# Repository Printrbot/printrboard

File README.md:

printrboard
===========

Reprap Electronics for the Printrbot

For more info see the Reprap wiki page http://reprap.org/wiki/Printrboard

The BoM with Digikey P/N's is available here: https://goo.gl/G4QnvK

This project, and all of its design files (including the layout), is licensed under the [Creative Commons Attribution-ShareAlike 3.0 Unported](http://creativecommons.org/licenses/by-sa/3.0/) license.

Anyone found to be in violation of this license may not produce or discribute any products using these designs, and will have legal action taken against them.

If you do end up producing boards commercially, a donation of 5% of the retail price or $4 per board would greatly be appreciated. Paypal (lwalkera at ieee.org), or bitcoin 1Cy1JwPiEEVS1RYxfHHFcmJMKbFNrb1Nqd work the best.

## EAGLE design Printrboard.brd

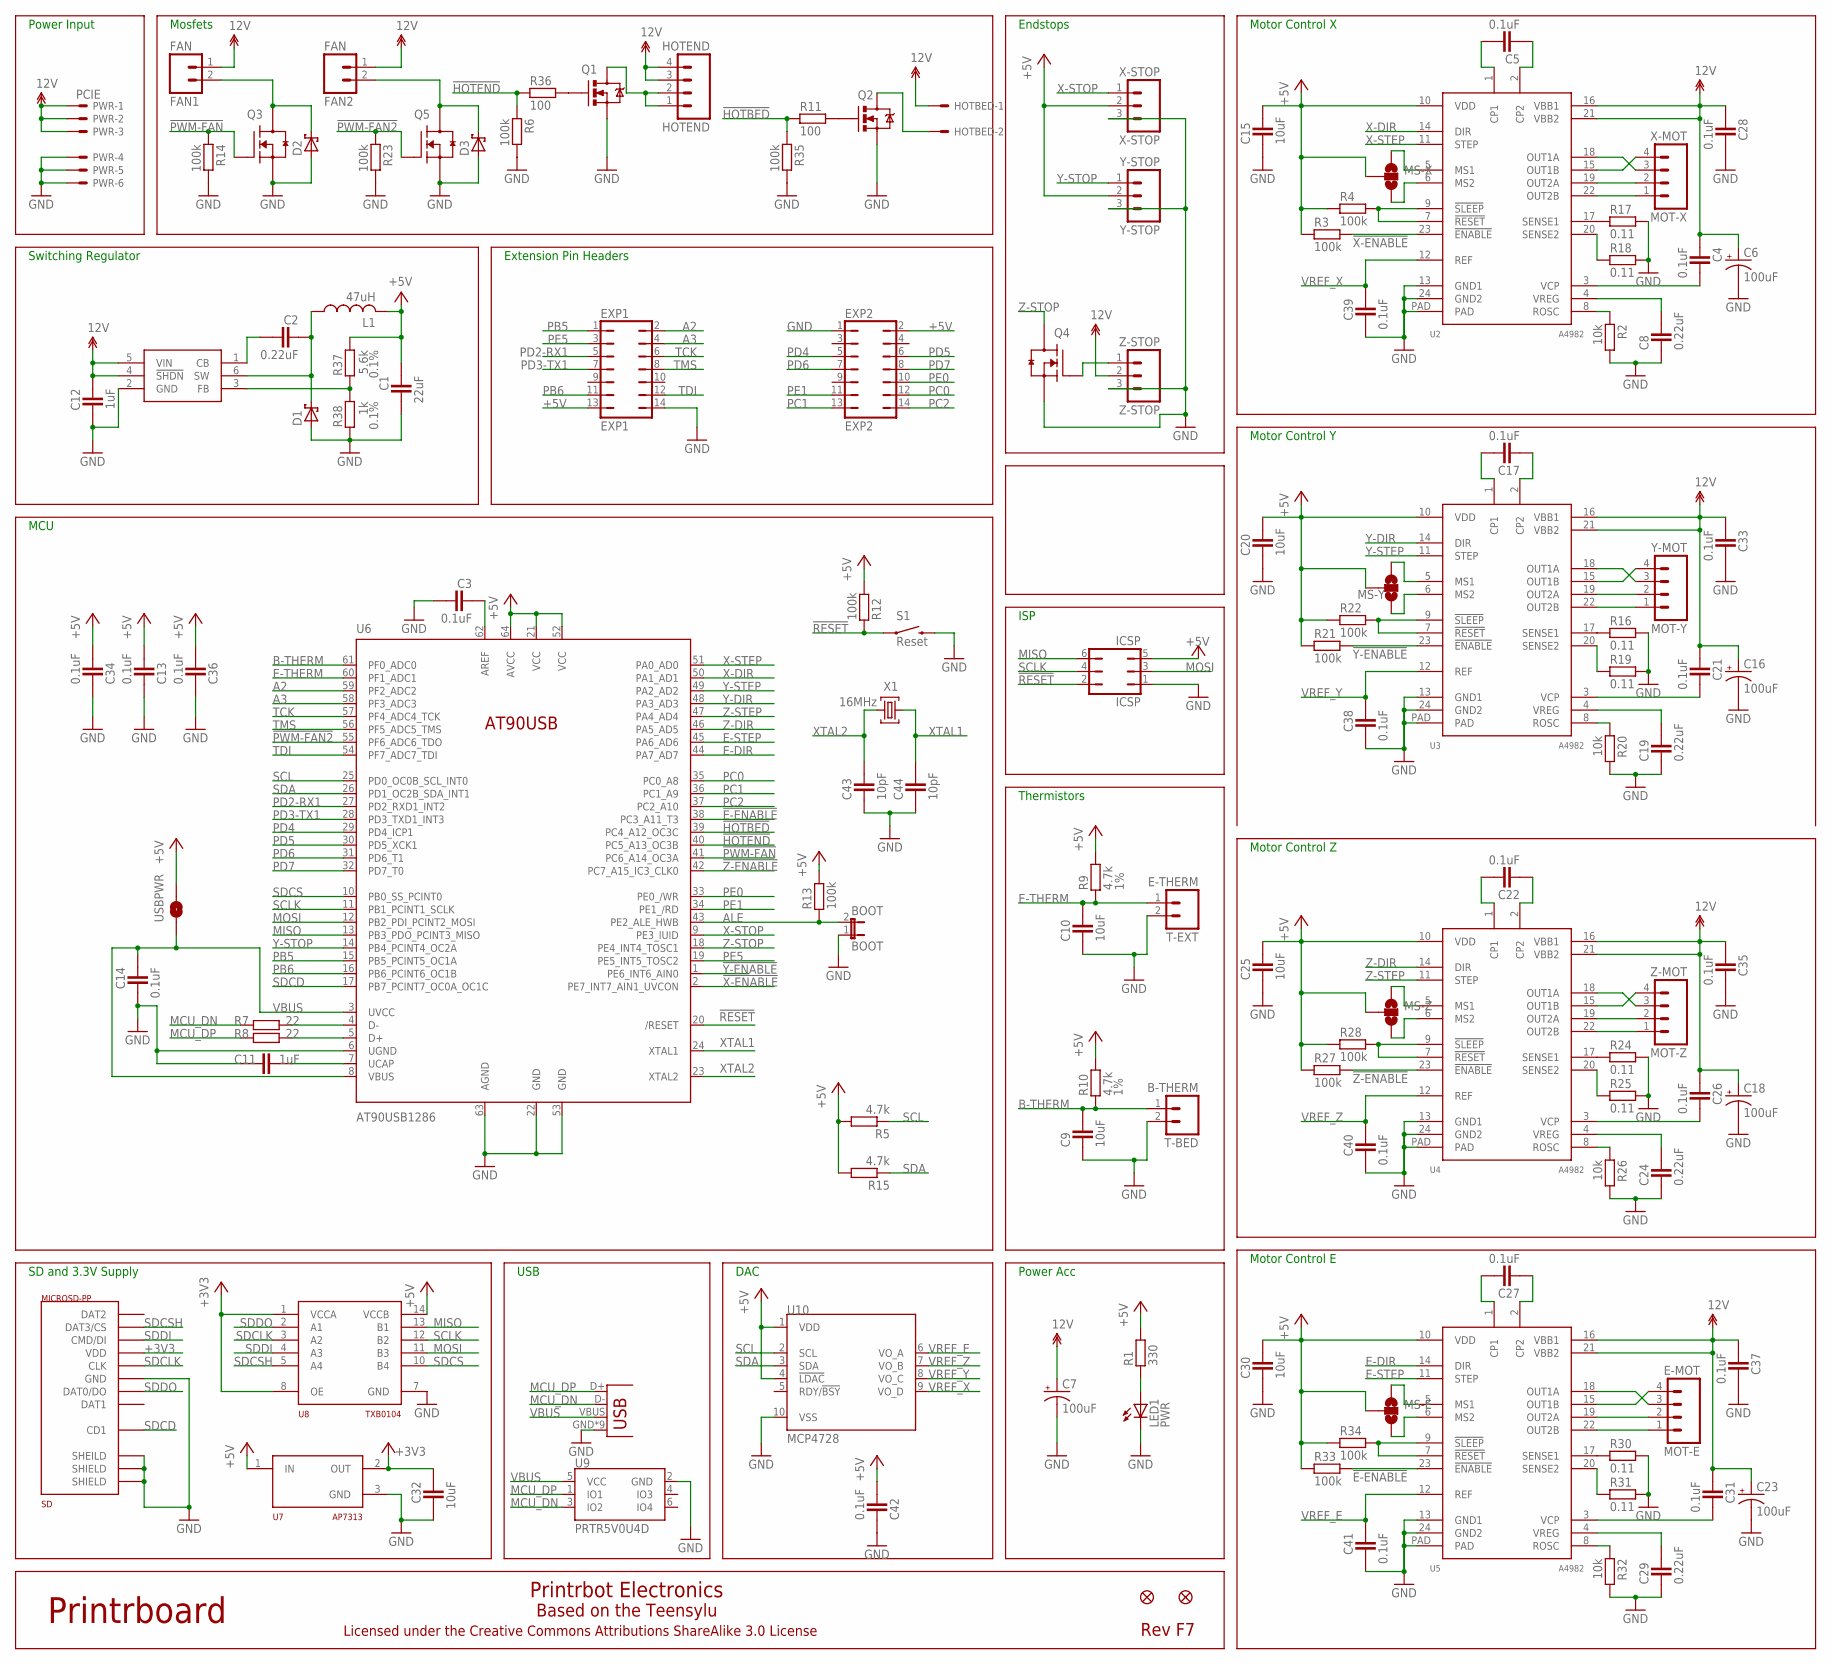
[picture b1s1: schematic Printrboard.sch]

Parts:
BOOT: BOOT; 1X02
C1: 22uF; CAPC2012X145AN
C2, C8, C19, C24, C29: 0.22uF; CAPC2012X145AN
C3, C4, C5, C13, C14, C17, C21, C22, C26, C27, C28, C31, C33, C34, C35, C36, C37, C38, C39, C40, C41, C42: 0.1uF; CAPC2012X145AN
C6, C7, C16, C18, C23: 100uF; PANASONIC_D
C9, C10, C15, C20, C25, C30, C32: 10uF; CAPC2012X145AN
C11, C12: 1uF; CAPC2012X145AN
C43, C44: 10pF; CAPC2012X145AN
D1, D2, D3: SCH-DIODESMA; SMA
E-MOT: MOT-E; MOLEX-1X4
EXP1: EXP1; JP7Q
EXP2: EXP2; JP7Q
FAN1, FAN2: FAN; 1X02
HOTBED: PHOENIX-2POS-5MM-SCREW; PHOENIX-5MM-2POS
HOTEND: HOTEND; MOLEX-1X4
ICSP: ICSP; JP3Q
JP26, JP33: FIDUCIAL1X2.5; FIDUCIAL-1X2.5
L1: 47uH; SDR1006
LED1: PWR; CHIP-LED0805
MS-E: SOLDERJUMPER_2WAYCONNECTED; SJ_3_CONNECTED
MS-X: SOLDERJUMPER_2WAYCONNECTED; SJ_3_CONNECTED
MS-Y: SOLDERJUMPER_2WAYCONNECTED; SJ_3_CONNECTED
MS-Z: SOLDERJUMPER_2WAYCONNECTED; SJ_3_CONNECTED
PWR: PCIE; 5566-6
Q1, Q2: RFP30N06LE; TO220V
Q3, Q4, Q5: RFP30N06LE; SOT95P280X135-3N
R1: 330; RESC2012X70N
R2, R20, R26, R32: 10k; RESC2012X70N
R3, R4, R6, R12, R13, R14, R21, R22, R23, R27, R28, R33, R34, R35: 100k; RESC2012X70N
R5, R15: 4.7k; RESC2012X70N
R7, R8: 22; RESC2012X70N
R9, R10: 4.7k; RESC2012X70N; TOLERANCE 1%
R11, R36: 100; RESC2012X70N
R16, R17, R18, R19, R24, R25, R30, R31: 0.11; RESC2012X70N
R37: 5.6k; RESC2012X70N; TOLERANCE 0.1%
R38: 1k; RESC2012X70N; TOLERANCE 0.1%
S1: Reset; TACTILE_SWITCH_TALL
SD: MICROSD-PP; USD-101-00660-68-6
T-BED: B-THERM; 1X02
T-EXT: E-THERM; 1X02
U1: LM2841; TSOT6
U2, U3, U4, U5: A4982; TSSOP-24
U6: AT90USB1286; TQFP64-2
U7: AP7313; SOT23C
U8: TXB0104; TSSOP14
U9: PRTR5V0U4D; SOT23-6
U10: MCP4728; MSOP10
USB-M: USB-MICRO-PTH; USB-MICROB-PTH
USBPWR: SOLDERJUMPERNO; SJ_2S-NO
X1: 16MHz; NDK-XTAL
X-MOT: MOT-X; MOLEX-1X4
X-STOP: X-STOP; MOLEX-1X3
Y-MOT: MOT-Y; MOLEX-1X4
Y-STOP: Y-STOP; MOLEX-1X3
Z-MOT: MOT-Z; MOLEX-1X4
Z-STOP: Z-STOP; MOLEX-1X3

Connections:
12V: C4.1, C6.+, C7.+, C12.1, C16.+, C18.+, C21.1, C23.+, C26.1, C28.1, C31.1, C33.1, C35.1, C37.1, FAN1.1, FAN2.1, HOTBED.P$1, HOTEND.3, HOTEND.4, PWR.1, PWR.2, PWR.3, U1.4 (!SHDN), U1.5 (VIN), U2.16 (VBB1), U2.21 (VBB2), U3.16 (VBB1), U3.21 (VBB2), U4.16 (VBB1), U4.21 (VBB2), U5.16 (VBB1), U5.21 (VBB2), Z-STOP.2
!E-ENABLE: R33.2, U5.23 (!ENABLE), U6.38 (PC3_A11_T3)
!HOTBED: R11.1, R35.1, U6.39 (PC4_A12_OC3C)
!HOTEND: R6.1, R36.1, U6.40 (PC5_A13_OC3B)
!PWM-FAN: Q3.1 (G), R14.1, U6.41 (PC6_A14_OC3A)
!PWM-FAN2: Q5.1 (G), R23.1, U6.55 (PF6_ADC6_TDO)
!RESET: ICSP.2, R12.1, S1.A2 (1), U6.20 (/RESET)
!X-ENABLE: R3.2, U2.23 (!ENABLE), U6.2 (PE7_INT7_AIN1_UVCON)
!Y-ENABLE: R21.2, U3.23 (!ENABLE), U6.1 (PE6_INT6_AIN0)
!Z-ENABLE: R27.2, U4.23 (!ENABLE), U6.42 (PC7_A15_IC3_CLK0)
+3V3: C32.1, SD.P$4 (VDD), U7.2 (OUT), U8.1 (VCCA), U8.8 (OE)
+5V: C1.1, C13.2, C15.2, C20.2, C25.2, C30.2, C34.2, C36.2, C42.2, EXP1.13, EXP2.2, ICSP.5, L1.P$2 (2), MS-E.2, MS-X.2, MS-Y.2, MS-Z.2, R1.2, R3.1, R4.1, R5.2, R9.2, R10.2, R12.2, R13.2, R15.2, R21.1, R22.1, R27.1, R28.1, R33.1, R34.1, R37.1, U2.10 (VDD), U3.10 (VDD), U4.10 (VDD), U5.10 (VDD), U6.21 (VCC), U6.52 (VCC), U6.64 (AVCC), U7.1 (IN), U8.14 (VCCB), U10.1 (VDD), U10.4 (!LDAC), USBPWR.2, X-STOP.2, Y-STOP.2
A2: EXP1.2, U6.59 (PF2_ADC2)
A3: EXP1.4, U6.58 (PF3_ADC3)
ALE: BOOT.2, R13.1, U6.43 (PE2_ALE_HWB)
AREF: C3.1, U6.62 (AREF)
B-THERM: C9.2, R10.1, T-BED.1, U6.61 (PF0_ADC0)
E-DIR: U5.14 (DIR), U6.44 (PA7_AD7)
E-STEP: U5.11 (STEP), U6.45 (PA6_AD6)
E-THERM: C10.2, R9.1, T-EXT.1, U6.60 (PF1_ADC1)
GND: BOOT.1, C1.2, C3.2, C6.-, C7.-, C8.1, C9.1, C10.1, C11.1, C12.2, C13.1, C14.2, C15.1, C16.-, C18.-, C19.1, C20.1, C23.-, C24.1, C25.1, C28.2, C29.1, C30.1, C32.2, C33.2, C34.1, C35.2, C36.1, C37.2, C38.2, C39.2, C40.2, C41.2, C42.1, C43.1, C44.1, D1.A, D2.A, D3.A, EXP1.14, EXP2.1, ICSP.1, LED1.C, PWR.4, PWR.5, PWR.6, Q1.3 (S), Q2.3 (S), Q3.2 (S), Q4.2 (S), Q5.2 (S), R2.2, R6.2, R14.2, R16.2, R17.2, R18.2, R19.2, R20.2, R23.2, R24.2, R25.2, R26.2, R30.2, R31.2, R32.2, R35.2, R38.2, S1.B2 (2), SD.GND1 (SHEILD), SD.GND2 (SHIELD), SD.GND3 (SHIELD), SD.P$6 (GND), T-BED.2, T-EXT.2, U1.2 (GND), U2.13 (GND1), U2.24 (GND2), U2.PAD, U3.13 (GND1), U3.24 (GND2), U3.PAD, U4.13 (GND1), U4.24 (GND2), U4.PAD, U5.13 (GND1), U5.24 (GND2), U5.PAD, U6.6 (UGND), U6.22 (GND), U6.53 (GND), U6.63 (AGND), U7.3 (GND), U8.7 (GND), U9.2 (GND), U10.10 (VSS), USB-M.GND, USB-M.GND1 (GND), USB-M.GND2 (GND), USB-M.GND3 (GND), USB-M.GND4 (GND), USB-M.GND5 (GND), USB-M.GND6 (GND), USB-M.GND7 (GND), USB-M.GND8 (GND), X-STOP.3, Y-STOP.3, Z-STOP.3
HOTBED-GND: HOTBED.P$2, Q2.2 (D)
HOTEND-GND: HOTEND.1, HOTEND.2, Q1.2 (D)
MCU_DN: R7.1, U9.3 (IO2), USB-M.D-
MCU_DP: R8.1, U9.1 (IO1), USB-M.D+
MISO: ICSP.6, U6.13 (PB3_PDO_PCINT3_MISO), U8.13 (B1)
MOSI: ICSP.3, U6.12 (PB2_PDI_PCINT2_MOSI), U8.11 (B3)
unnamed: LED1.A, R1.1
unnamed: D2.C, FAN1.2, Q3.3 (D)
unnamed: R7.2, U6.4 (D-)
unnamed: R8.2, U6.5 (D+)
unnamed: Q4.1 (G), Z-STOP.1
unnamed: Q2.1 (G), R11.2
unnamed: D3.C, FAN2.2, Q5.3 (D)
unnamed: C11.2, U6.7 (UCAP)
unnamed: U2.18 (OUT1A), X-MOT.3
unnamed: C5.2, U2.1 (CP1)
unnamed: C5.1, U2.2 (CP2)
unnamed: R2.1, U2.8 (ROSC)
unnamed: R17.1, U2.17 (SENSE1)
unnamed: R18.1, U2.20 (SENSE2)
unnamed: C4.2, U2.3 (VCP)
unnamed: U2.15 (OUT1B), X-MOT.4
unnamed: C8.2, U2.4 (VREG)
unnamed: U2.19 (OUT2A), X-MOT.2
unnamed: R4.2, U2.7 (!RESET), U2.9 (!SLEEP)
unnamed: R37.2, R38.1, U1.3 (FB)
unnamed: U2.22 (OUT2B), X-MOT.1
unnamed: U3.19 (OUT2A), Y-MOT.2
unnamed: U3.22 (OUT2B), Y-MOT.1
unnamed: U3.15 (OUT1B), Y-MOT.4
unnamed: MS-X.1, U2.5 (MS1)
unnamed: MS-X.3, U2.6 (MS2)
unnamed: C17.2, U3.1 (CP1)
unnamed: C17.1, U3.2 (CP2)
unnamed: U3.18 (OUT1A), Y-MOT.3
unnamed: R19.1, U3.20 (SENSE2)
unnamed: R20.1, U3.8 (ROSC)
unnamed: C19.2, U3.4 (VREG)
unnamed: R22.2, U3.7 (!RESET), U3.9 (!SLEEP)
unnamed: C21.2, U3.3 (VCP)
unnamed: R16.1, U3.17 (SENSE1)
unnamed: U4.15 (OUT1B), Z-MOT.4
unnamed: U4.18 (OUT1A), Z-MOT.3
unnamed: U4.19 (OUT2A), Z-MOT.2
unnamed: MS-Y.1, U3.5 (MS1)
unnamed: MS-Y.3, U3.6 (MS2)
unnamed: C22.2, U4.1 (CP1)
unnamed: C22.1, U4.2 (CP2)
unnamed: R24.1, U4.17 (SENSE1)
unnamed: R25.1, U4.20 (SENSE2)
unnamed: R26.1, U4.8 (ROSC)
unnamed: C24.2, U4.4 (VREG)
unnamed: R28.2, U4.7 (!RESET), U4.9 (!SLEEP)
unnamed: C26.2, U4.3 (VCP)
unnamed: U4.22 (OUT2B), Z-MOT.1
unnamed: E-MOT.4, U5.15 (OUT1B)
unnamed: E-MOT.3, U5.18 (OUT1A)
unnamed: E-MOT.2, U5.19 (OUT2A)
unnamed: MS-Z.1, U4.5 (MS1)
unnamed: MS-Z.3, U4.6 (MS2)
unnamed: C27.2, U5.1 (CP1)
unnamed: C27.1, U5.2 (CP2)
unnamed: R30.1, U5.17 (SENSE1)
unnamed: R31.1, U5.20 (SENSE2)
unnamed: R32.1, U5.8 (ROSC)
unnamed: C29.2, U5.4 (VREG)
unnamed: R34.2, U5.7 (!RESET), U5.9 (!SLEEP)
unnamed: C31.2, U5.3 (VCP)
unnamed: E-MOT.1, U5.22 (OUT2B)
unnamed: Q1.1 (G), R36.2
unnamed: MS-E.1, U5.5 (MS1)
unnamed: MS-E.3, U5.6 (MS2)
unnamed: C2.1, D1.C, L1.P$1 (1), U1.6 (SW)
unnamed: C2.2, U1.1 (CB)
PB5: EXP1.1, U6.15 (PB5_PCINT5_OC1A)
PB6: EXP1.11, U6.16 (PB6_PCINT6_OC1B)
PC0: EXP2.12, U6.35 (PC0_A8)
PC1: EXP2.13, U6.36 (PC1_A9)
PC2: EXP2.14, U6.37 (PC2_A10)
PD2-RX1: EXP1.5, U6.27 (PD2_RXD1_INT2)
PD3-TX1: EXP1.7, U6.28 (PD3_TXD1_INT3)
PD4: EXP2.5, U6.29 (PD4_ICP1)
PD5: EXP2.6, U6.30 (PD5_XCK1)
PD6: EXP2.7, U6.31 (PD6_T1)
PD7: EXP2.8, U6.32 (PD7_T0)
PE0: EXP2.10, U6.33 (PE0_/WR)
PE1: EXP2.11, U6.34 (PE1_/RD)
PE5: EXP1.3, U6.19 (PE5_INT5_TOSC2)
SCL: R5.1, U6.25 (PD0_OC0B_SCL_INT0), U10.2 (SCL)
SCLK: ICSP.4, U6.11 (PB1_PCINT1_SCLK), U8.12 (B2)
SDA: R15.1, U6.26 (PD1_OC2B_SDA_INT1), U10.3 (SDA)
SDCD: SD.CD (CD1), U6.17 (PB7_PCINT7_OC0A_OC1C)
SDCLK: SD.P$5 (CLK), U8.3 (A2)
SDCS: U6.10 (PB0_SS_PCINT0), U8.10 (B4)
SDCSH: SD.P$2 (DAT3/CS), U8.5 (A4)
SDDI: SD.P$3 (CMD/DI), U8.4 (A3)
SDDO: SD.P$7 (DAT0/DO), U8.2 (A1)
TCK: EXP1.6, U6.57 (PF4_ADC4_TCK)
TDI: EXP1.12, U6.54 (PF7_ADC7_TDI)
TMS: EXP1.8, U6.56 (PF5_ADC5_TMS)
VBUS: C14.1, U6.3 (UVCC), U6.8 (VBUS), U9.5 (VCC), USB-M.VBUS, USBPWR.1
VREF_E: C41.1, U5.12 (REF), U10.6 (VO_A)
VREF_X: C39.1, U2.12 (REF), U10.9 (VO_D)
VREF_Y: C38.1, U3.12 (REF), U10.8 (VO_C)
VREF_Z: C40.1, U4.12 (REF), U10.7 (VO_B)
X-DIR: U2.14 (DIR), U6.50 (PA1_AD1)
X-STEP: U2.11 (STEP), U6.51 (PA0_AD0)
X-STOP: U6.9 (PE3_IUID), X-STOP.1
XTAL1: C44.2, U6.24 (XTAL1), X1.P$1 (1)
XTAL2: C43.2, U6.23 (XTAL2), X1.P$2 (2)
Y-DIR: U3.14 (DIR), U6.48 (PA3_AD3)
Y-STEP: U3.11 (STEP), U6.49 (PA2_AD2)
Y-STOP: U6.14 (PB4_PCINT4_OC2A), Y-STOP.1
Z-DIR: U4.14 (DIR), U6.46 (PA5_AD5)
Z-STEP: U4.11 (STEP), U6.47 (PA4_AD4)
Z-STOP: Q4.3 (D), U6.18 (PE4_INT4_TOSC1)

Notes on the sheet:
Motor Control X
Motor Control Y
Motor Control Z
Motor Control E
ISP
Thermistors
Endstops
Mosfets
Power Acc
Printrboard
Rev F7
Printrbot Electronics
Licensed under the Creative Commons Attributions ShareAlike 3.0 License
Extension Pin Headers
Switching Regulator
Based on the Teensylu
SD and 3.3V Supply
Power Input
MCU
USB
DAC

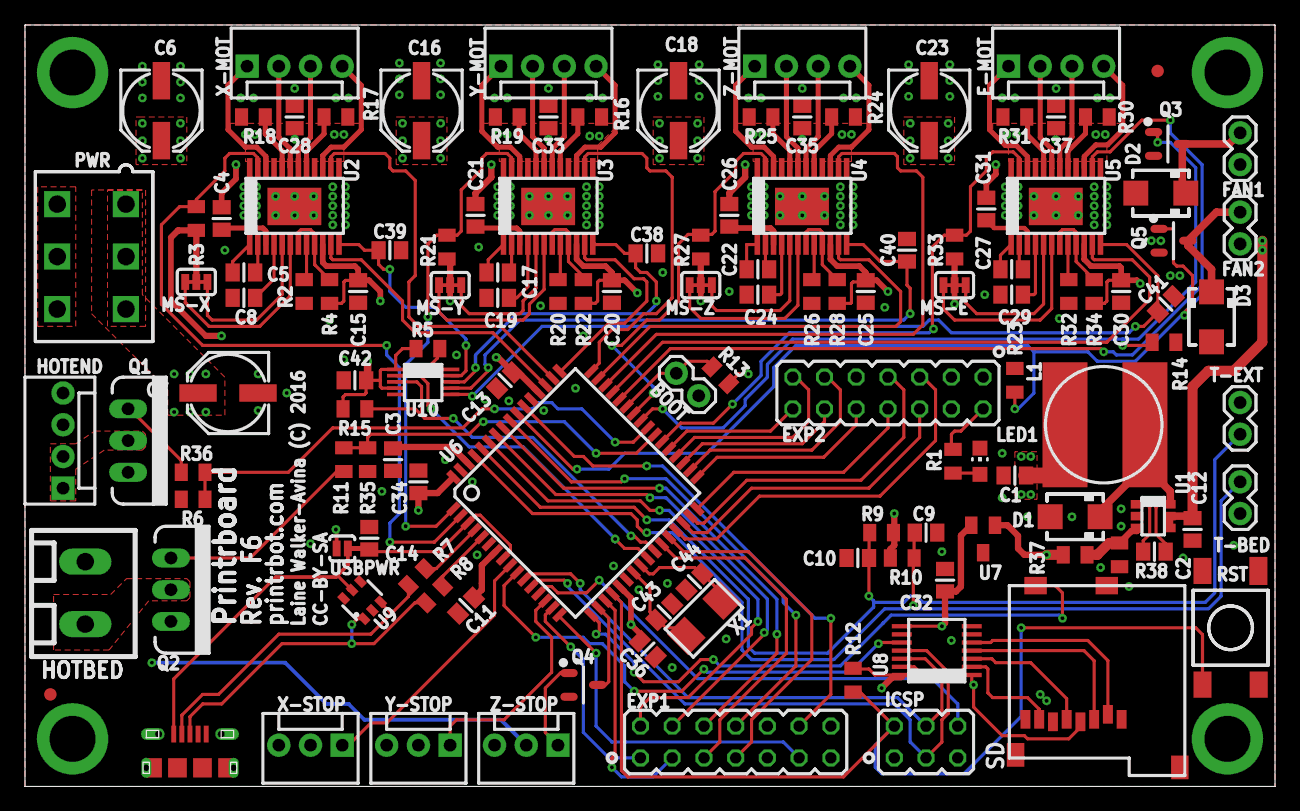
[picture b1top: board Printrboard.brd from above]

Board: 4 copper layers, 100.1 x 61.0 mm, 130 parts (0 on the bottom side), 137 nets.

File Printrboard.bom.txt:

Partlist exported from C:/Users/Ceriand/Dropbox/eagle/printrboard/Printrboard.sch at 11/20/2011 6:06:26 PM

Qty Value         Device              Parts                                                       
  
*1                 SCH-DIODESMA        D1                                                          
*11  0.1uF         CAPACITOR_0805      C3, C4, C5, C13, C14, C17, C21, C22, C26, C27, C31          
*8   0.22          RESISTOR_0805       R16, R17, R18, R19, R24, R25, R30, R31                      
*5   0.22uF        CAPACITOR_0805      C8, C19, C24, C29, C2                                           
*1   1k            RESISTOR_0805       R37                                          
*2   1uF           CAPACITOR_0805      C12, C11 
*1   3.32k         RESISTOR_0805       R38                                                         
*2   4.7k          RESISTOR_0805       R9, R10                                                     
*1   8MHz          AWSCR-CV            X1                                                          
*3   100           RESISTOR_0805       R11, R36, R1                                                    
*4   10k           RESISTOR_0805       R2, R20, R26, R32                                           
*4   10k           RTRIM-ST-4EA        R5, R15, R23, R29                                           
*6   10uF          CAPACITOR_0805      C9, C10, C15, C20, C25, C30                                 
*2   22            RESISTOR_0805       R7, R8                                                      
*1   22uF          CAPACITOR_0805      C1                                                          
*1   47uH          L-US                L1                                                          
*13  100k          RESISTOR_0805       R3, R4, R6, R12, R13, R14, R21, R22, R27, R28, R33, R34, R35
*4   100uF         CPOL-USD            C6, C16, C18, C23  
*1   680uF         CPOL-USF            C7                                                          
*4   A4982         A4982               U2, U3, U4, U5                               
*1   AT90USB1286   AT90USB             IC2                             
*1   LM2841        LM2841              U1                                                          
*1   MICROSD       MICROSD             J1                            
*1   PWR           LEDCHIP-LED0805     LED2                                                        
*2   RFP30N06LE    MOSFET-NCHANNELPTH2 Q1, Q2                                                      
*1   RFP30N06LE    MOSFET-NCH_SOT-23   Q3 

                                                         
*1   Reset         SWITCH-MOMENTARY-2  S2                                                          
*1   USB-MICROB    USB-MICROB          J2        
2   2x7           JP7Q                JP2, JP35 
1                 JP3Q                JP4                                                         
8                 JUMPER-2PTH         E-MS1, E-MS2, X-MS1, X-MS2, Y-MS1, Y-MS2, Z-MS1, Z-MS2
4   MOT-X         M04POLAR            JP1, JP3, JP5, JP9     
*1   ATX           5566-4              J3   
1   X-STOP        M03POLAR            JP27                                                        
1   Y-STOP        M03POLAR            JP28                                                        
1   Z-STOP        M03POLAR            JP29                                                        
1   B-THERM       M02PTH              JP24                                                        
1   E-STOP        M03POLAR            JP30                                                        
1   E-THERM       M02PTH              JP22                                                        
1   FAN           M02PTH              JP25                                                        
2   FIDUCIAL1X2.5 FIDUCIAL1X2.5       JP26, JP33                                                  
1   HOTBED        M04POLAR            JP21                                                        
1   HOTEND        M04POLAR            JP8    
1   ALE           JUMPER-2PTH         JP32

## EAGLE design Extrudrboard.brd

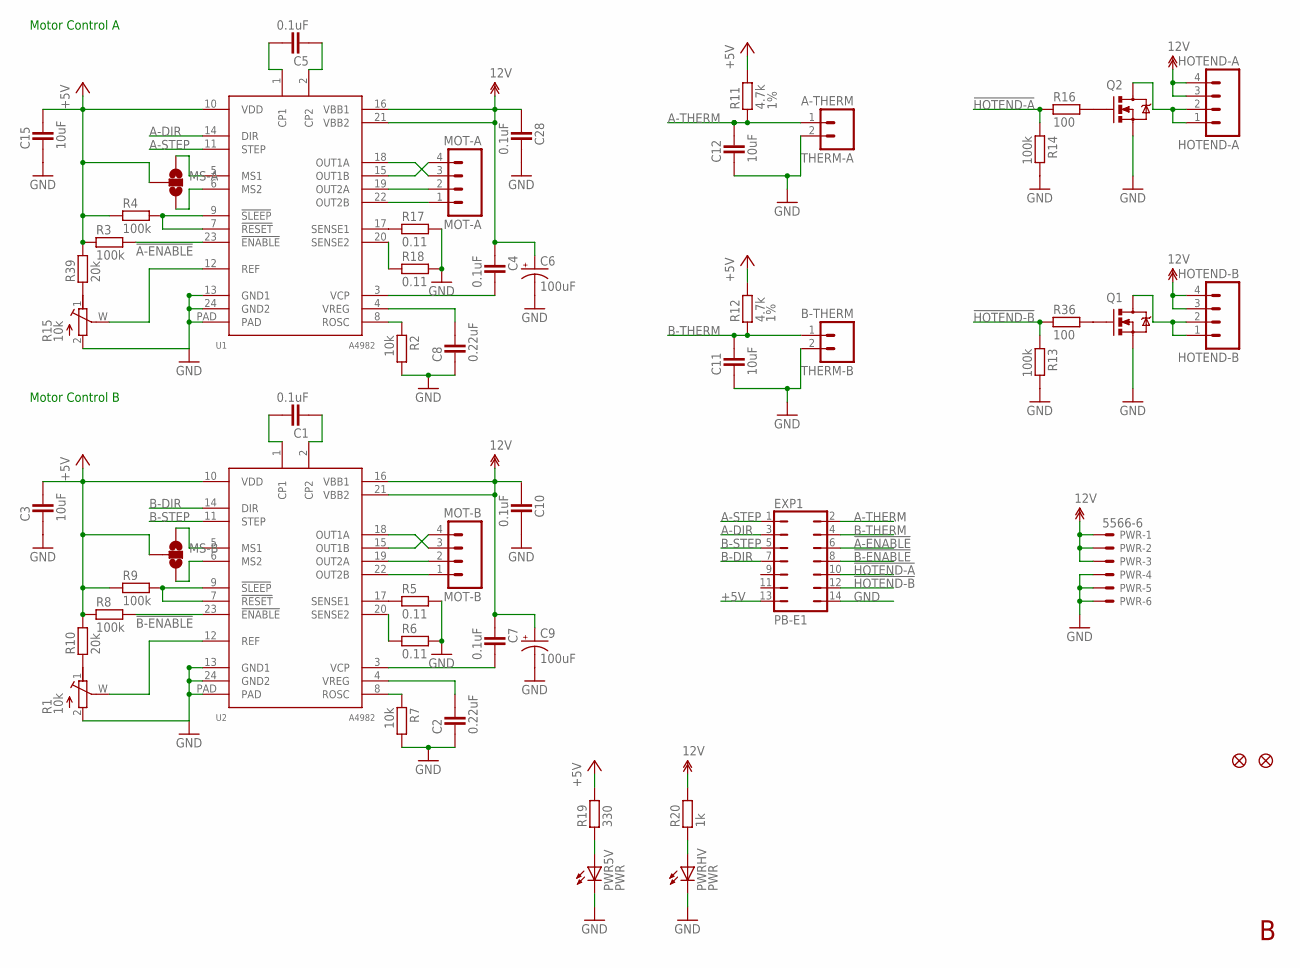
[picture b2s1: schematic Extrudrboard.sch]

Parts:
C1, C4, C5, C7, C10, C28: 0.1uF; CAPC2012X145AN
C2, C8: 0.22uF; CAPC2012X145AN
C3, C11, C12, C15: 10uF; CAPC2012X145AN
C6, C9: 100uF; PANASONIC_D
EXP1: PB-E1; JP7Q
HOTEND-A: HOTEND-A; MOLEX-1X4
HOTEND-B: HOTEND-B; MOLEX-1X4
JP1, JP2: FIDUCIAL1X2.5; FIDUCIAL-1X2.5
MOT-A: MOT-A; MOLEX-1X4
MOT-B: MOT-B; MOLEX-1X4
MS-A: SOLDERJUMPER_2WAYCONNECTED; SJ_3_CONNECTED
MS-B: SOLDERJUMPER_2WAYCONNECTED; SJ_3_CONNECTED
PWR: 5566-6
PWR5V: PWR; CHIP-LED0805
PWRHV: PWR; CHIP-LED0805
Q1, Q2: MOSFET-NCHANNELPTH2; TO220V
R1, R15: 10k; RTRIM-ST4ETB
R2, R7: 10k; RESC2012X70N
R3, R4, R8, R9, R13, R14: 100k; RESC2012X70N
R5, R6, R17, R18: 0.11; RESC2012X70N
R10, R39: 20k; RESC2012X70N
R11, R12: 4.7k; RESC2012X70N; TOLERANCE 1%
R16, R36: 100; RESC2012X70N
R19: 330; RESC2012X70N
R20: 1k; RESC2012X70N
THERM-A: A-THERM; 1X02
THERM-B: B-THERM; 1X02
U1, U2: A4982; TSSOP-24

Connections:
12V: C4.1, C6.+, C7.1, C9.+, C10.1, C28.1, HOTEND-A.3, HOTEND-A.4, HOTEND-B.3, HOTEND-B.4, PWR.1, PWR.2, PWR.3, R20.2, U1.16 (VBB1), U1.21 (VBB2), U2.16 (VBB1), U2.21 (VBB2)
!A-ENABLE: EXP1.6, R3.2, U1.23 (!ENABLE)
!B-ENABLE: EXP1.8, R8.2, U2.23 (!ENABLE)
!HOTEND-A: EXP1.10, R14.1, R16.1
!HOTEND-B: EXP1.12, R13.1, R36.1
+5V: C3.2, C15.2, EXP1.13, MS-A.2, MS-B.2, R3.1, R4.1, R8.1, R9.1, R10.2, R11.2, R12.2, R19.2, R39.2, U1.10 (VDD), U2.10 (VDD)
A-DIR: EXP1.3, U1.14 (DIR)
A-STEP: EXP1.1, U1.11 (STEP)
A-THERM: C12.2, EXP1.2, R11.1, THERM-A.1
B-DIR: EXP1.7, U2.14 (DIR)
B-STEP: EXP1.5, U2.11 (STEP)
B-THERM: C11.2, EXP1.4, R12.1, THERM-B.1
GND: C2.1, C3.1, C6.-, C8.1, C9.-, C10.2, C11.1, C12.1, C15.1, C28.2, EXP1.14, PWR.4, PWR.5, PWR.6, PWR5V.C, PWRHV.C, Q1.3 (S), Q2.3 (S), R1.2 (E), R2.2, R5.2, R6.2, R7.2, R13.2, R14.2, R15.2 (E), R17.2, R18.2, THERM-A.2, THERM-B.2, U1.13 (GND1), U1.24 (GND2), U1.PAD, U2.13 (GND1), U2.24 (GND2), U2.PAD
HOTENDA-GND: HOTEND-A.1, HOTEND-A.2, Q2.2 (D)
HOTENDB-GND: HOTEND-B.1, HOTEND-B.2, Q1.2 (D)
unnamed: C1.2, U2.1 (CP1)
unnamed: C1.1, U2.2 (CP2)
unnamed: R5.1, U2.17 (SENSE1)
unnamed: R6.1, U2.20 (SENSE2)
unnamed: R1.W (S), U2.12 (REF)
unnamed: R7.1, U2.8 (ROSC)
unnamed: C2.2, U2.4 (VREG)
unnamed: R9.2, U2.7 (!RESET), U2.9 (!SLEEP)
unnamed: C7.2, U2.3 (VCP)
unnamed: MOT-A.3, U1.18 (OUT1A)
unnamed: C5.2, U1.1 (CP1)
unnamed: C5.1, U1.2 (CP2)
unnamed: R2.1, U1.8 (ROSC)
unnamed: R17.1, U1.17 (SENSE1)
unnamed: R18.1, U1.20 (SENSE2)
unnamed: C4.2, U1.3 (VCP)
unnamed: MOT-A.4, U1.15 (OUT1B)
unnamed: R15.W (S), U1.12 (REF)
unnamed: C8.2, U1.4 (VREG)
unnamed: MOT-A.2, U1.19 (OUT2A)
unnamed: R4.2, U1.7 (!RESET), U1.9 (!SLEEP)
unnamed: MS-B.1, U2.5 (MS1)
unnamed: MOT-A.1, U1.22 (OUT2B)
unnamed: MS-B.3, U2.6 (MS2)
unnamed: MOT-B.3, U2.18 (OUT1A)
unnamed: MOT-B.4, U2.15 (OUT1B)
unnamed: MS-A.1, U1.5 (MS1)
unnamed: MS-A.3, U1.6 (MS2)
unnamed: MOT-B.2, U2.19 (OUT2A)
unnamed: MOT-B.1, U2.22 (OUT2B)
unnamed: R1.1 (A), R10.1
unnamed: Q2.1 (G), R16.2
unnamed: PWR5V.A, R19.1
unnamed: PWRHV.A, R20.1
unnamed: R15.1 (A), R39.1
unnamed: Q1.1 (G), R36.2

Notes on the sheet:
Motor Control A
Motor Control B

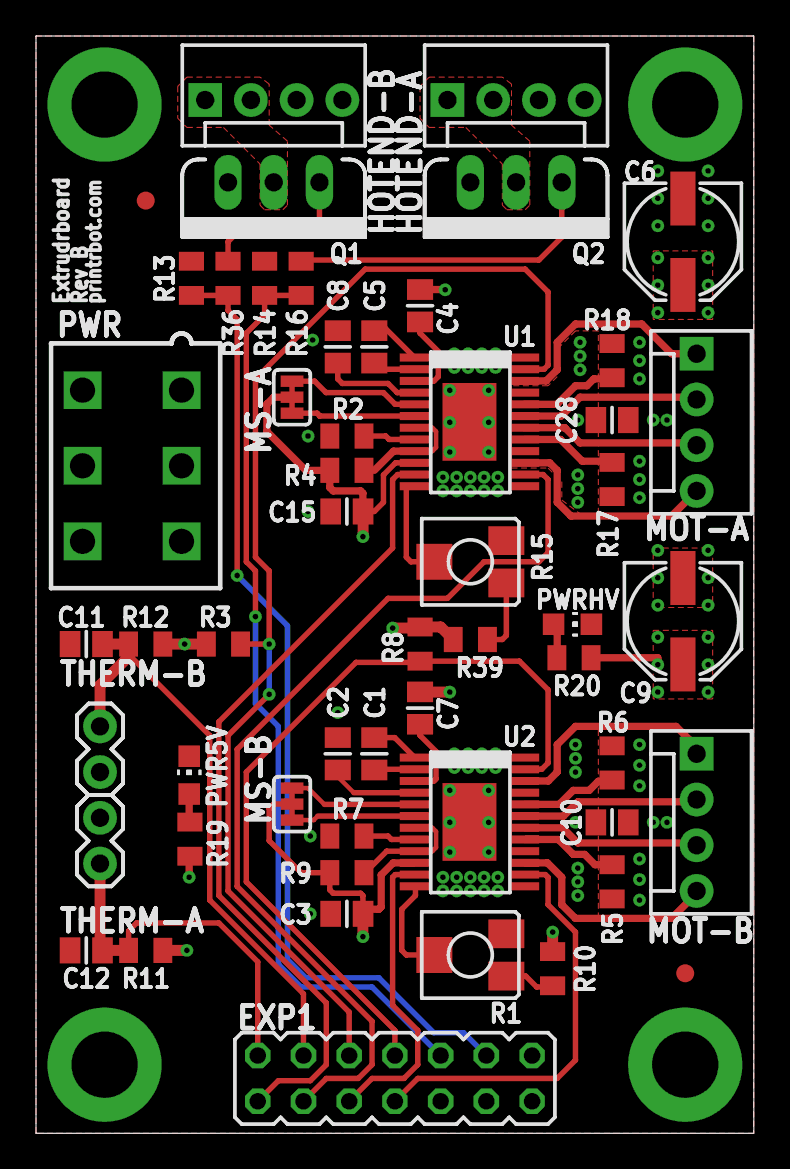
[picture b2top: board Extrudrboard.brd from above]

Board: 4 copper layers, 39.9 x 61.0 mm, 54 parts (0 on the bottom side), 51 nets.

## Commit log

2011-11-23 Fix some thermal, and angle errors. Add some additional caps on Vbb rail. More work on the silkscreen
2011-11-25 Add solder jumpers and move placement artwork for the Allegro package to tPlace
2011-11-25 Change to using solder jumpers for the microstepping selection
2011-11-30 Change thermal vias for the stepper driver, reduce paste area on drivers to 75%, make edge clearance 20 mils, and bring Vbb ceramic cap to top side
2011-11-30 Tweak the position of the motor traces
2011-12-03 Add text in tNames and tValues layers for Molex KK headers
2011-12-03 Copy level translator and LDO from SD adapter project in prep for 5V conversion
2011-12-03 Add resistors on all the Vref pots to allow for 5V change, and cleanup the silkscreen layers
2011-12-03 Update project file
2011-12-10 Change logic voltage to 5V, add translation circuitry for SD, move to 4-layer design, and cleanup some packages
2011-12-11 Tweak the board to pass 4pcb.com DFM
2011-12-16 Convert files to EAGLE 6
2012-01-02 Fix angle errors caused by 6.0 conversion, add more decoupling caps to MCU, and modify some routing
2012-01-16 Change some caps around, add a solder jumper for USB sourced 5V, and modify silkscreen for production
2012-01-19 Add extra solder pads for USB connector, and square up mounting holes
2012-04-03 Fixes for Rev C
    -Made all mounting holes the same size
    -Changed package for stepper solder jumpers to be connected by copper by
    default
2012-04-05 Board tweaks for rev D
    Move endstop connectors apart for more clearance and move the labels for
    the heaters around so they're easier to see
2012-05-03 Make resonator pad larger to accomodate both available pacakages, and change polarity of BOOT jumper
2012-05-28 Small layout tweaks for Rev D
    * Moved temp inputs closer to center of board and repositioned label so that
    they can be seen.
    * Gave the bottom expansion connector a little room by moving the ICSP port over a bit
    * Moved the cap next to the resonator a little farther away from each other
2012-12-31 Add in 6-pin PCIe power connector
2012-12-31 Fix values for sense resistors to match BoM
2013-06-11 Add gerber stuff to gitignore
2013-06-11 Add files for Extrudrboard Rev B
2013-10-23 Update files for Rev F
    Changed heatbed connector to 5mm pitch screw terminal
    Removed E-STOP connector
    Changed Y-STOP pin
    Moved former Y-STOP pin to SD interface to fix a limitation of the SPI ctlr
    Added I2C connector
    Replaced trimpots with 4-channel I2C DAC
2013-10-31 Manufacturability changes
    Added some pin 1 indicators
    Added test point for VBUS signal
2014-02-09 Update README with explicit license information
2014-05-22 Minor schematic changes
2014-06-03 Redraw USB connector for manufacturability
2014-07-10 Add in voltage selection and input buffering for the Z-stop
2015-01-15 Bump rev to F5 and update copyright date
2016-06-23 Rev F6
    Add second Fan port
    Add optional USB-B footprint
    Remove polyswitch
    Change to push-push microSD socket
2016-09-27 Add in changes requested by PBHQ
2017-06-20 Update README.md with better link to BoM

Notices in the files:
Extrudrboard.brd:
Laine Walker-Avina (C) 2013
Printrboard.brd:
Laine Walker-Avina (C) 2016
CC-BY-SA
